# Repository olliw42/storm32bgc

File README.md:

STorM32 BGC
===========

<strong>STM32 32-bit microcontroller based 3-axis brushless gimbal controller board</strong>

scheme and design by OlliW (except of STorM32 v4.1)<br>
v0.17: layout by Martinez and OlliW<br>
v4.1: design by KrattWorks

latest board version: v3.3, v4.1

the STorM32 BGC boards and all other hardware published here are open source hardware, under the terms of the TAPR Open Hardware License as published by the Free Hardware Foundation, see http://www.tapr.org/ohl.html

the firmwares are free and the GUI is open source, for the details of the terms of usage/licenses see <a href="http://www.olliw.eu/2013/storm32bgc">here</a>

<strong>further resources:</strong><br>- project web page http://www.olliw.eu/2013/storm32bgc/<br>- thread at rcgroups http://www.rcgroups.com/forums/showthread.php?t=2055844<br>- wiki for the documentation http://www.olliw.eu/storm32bgc-wiki/

## v4.1 Board

Board specifically made for NT and TSTorM32 setups, with on-board motor drivers.

## v3.3 Boards

Boards specifically made for NT and TSTorM32 setups.

### STorM32 v3.3m/i

General purpose version.

### STorM32 Raspberry Pi Hat

Hat for the Raspberry Pi.

### STorM32 Micro Series

Series of stackable boards with 20x20 mm hole pattern: Main board, NT Motor-Encoder module, NT Triple Motor module, NT Logger module. 

<strong>changes in v3.3:</strong><br>- board specifically designed for NT and T-STorM32<br>- no motor drivers on board<br>- 3 NT plugs to make it easy to connect several NT modules<br>- NT-X plug carrying also the battery voltage<br>- 5 V power rail on the NT bus, with sufficient "juice"<br>- Rx&Tx on NT bus swapped, to avoid cable crossing to connect with NT modules<br>- support of stacking with a "high-power" extension board<br>- MPU9250 on board, spi (no i2c anymore!)<br>- firmware update procedure via USB<br>- ESP8266 port for WIFI connectability<br>- CAN bus port<br>- no BOOT0 button, smaller RESET button<br>- 0402 size parts<br>- board size as small as I could get it with a 2 layer design: 40 x 25 mm<br>- mounting holes, 3 mm diameter, 35 mm apart

## v1.x Boards

<strong>changes in v1.3:</strong><br>- voltage regulator in DPak package<br>- AUX2 instead of 3.3V pin at AUX port<br>- solder jumper to disconnect bluetooth led<br>- values of resistors R12,R13,R22 changed
<br><strong>changes in v1.2:</strong><br>- minor issues of v1.1 corrected<br>- Futaba S-bus support<br>- Spektrum sattelite connector<br>- usb disconnect network modified to suite F4 processors (thanks ala42!)<br>- usb voltage protection diode added (as in v0.17)<br>- further minor changes in scheme and layout
<br><strong>changes in v1.1:</strong><br>- reverse voltage protection added<br>- layout supports TC4452 motor drivers in DFN package for increased power capabilities<br>- high-side pnp open collector output for driving an IR led added<br>- additional connector for I2C#2 port added<br>- larger solder holes and pads for battery power connection<br>- improved pin arrangement for easier use

## Pictures

<strong>pictures of the v2.4 board</strong><br>

<strong>pictures of the v1.2 board (with DFN packages) and v1.3 board (with SOIC packages):</strong><br>

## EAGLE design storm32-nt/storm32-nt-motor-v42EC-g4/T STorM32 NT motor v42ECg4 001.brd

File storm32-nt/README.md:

STorM32 Boards NT Series and NT Modules
==============

Schemes and designs by OlliW (with exceptin of the STorM32 v4.1 board). The STorM32 v4.1 board is design by [KrattWorks](https://www.krattworks.com/), [2](https://bitbucket.org/teamkrattworks/hw_storm32_v4/src/master/release/storm32-nt-v4_1/).<br>

The STorM32 boards offered in this folder are published as open source hardware, under the terms of the TAPR Open Hardware License as published by the Free Hardware Foundation, see http://www.tapr.org/ohl.html.

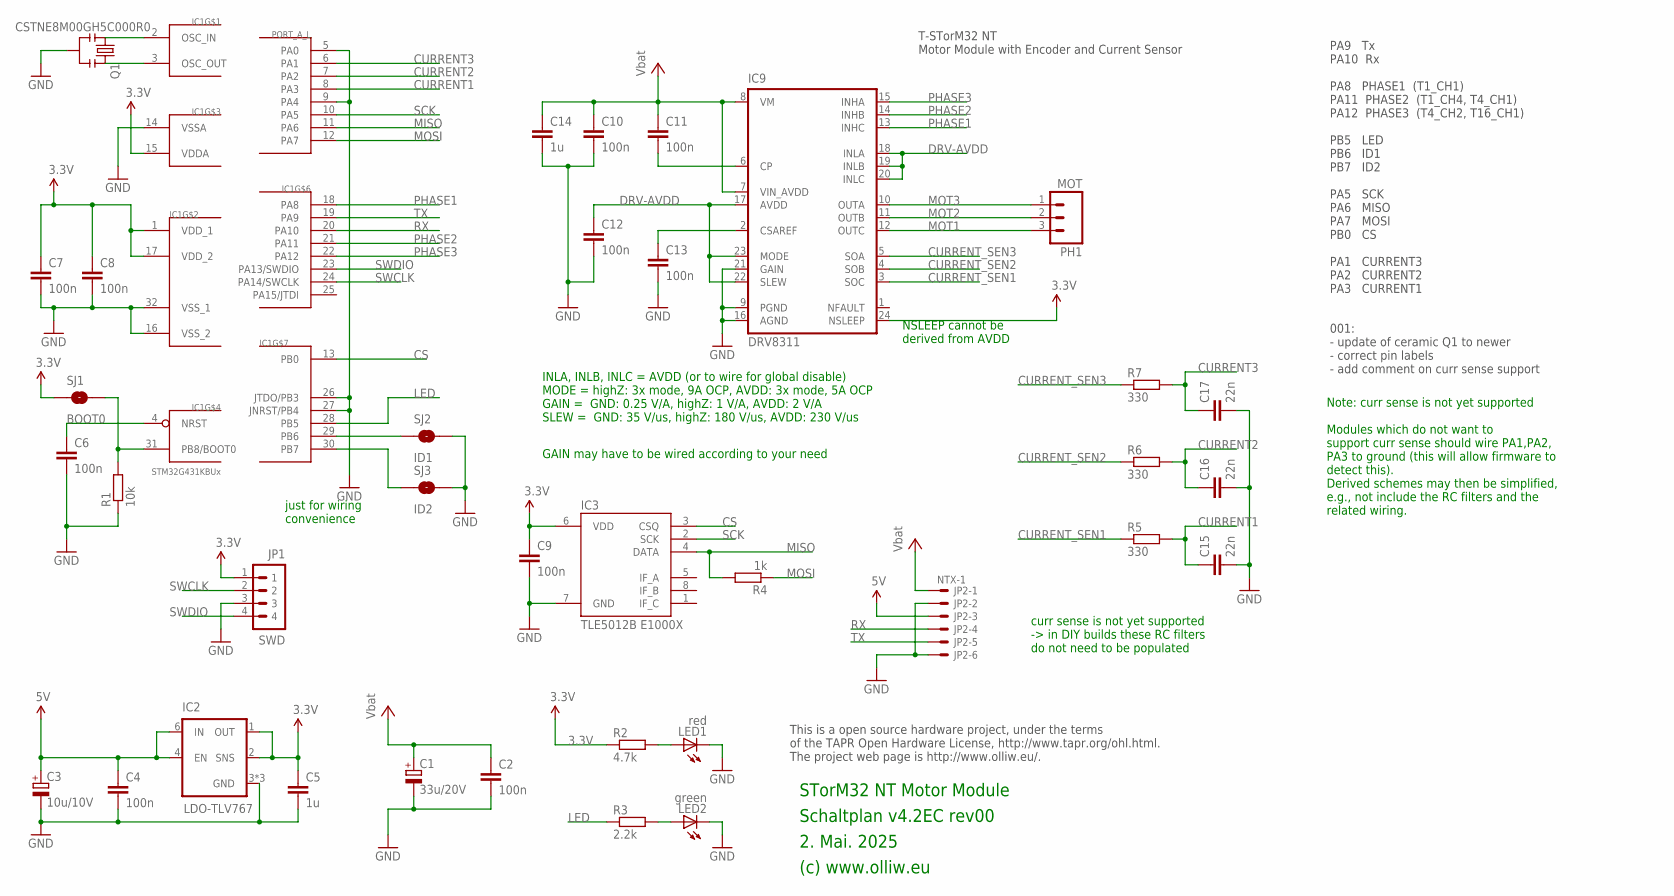
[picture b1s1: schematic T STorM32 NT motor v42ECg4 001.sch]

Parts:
C1: 33u/20V; SMC_C
C2, C4: 100n; C0603
C3: 10u/10V; SMC_B
C5, C14: 1u; C0603
C6, C7, C8, C9, C10, C11, C12, C13: 100n; C0402
C15, C16, C17: 22n; C0402
IC1: STM32G431KBUx; UFQFPN32
IC2: LDO-TLV767; WSON-6-2X2
IC3: TLE5012B E1000X; SO08
IC9: DRV8311; QFN(WQFN)24-3X3-DRV8311
JP1: SWD; 4X1_1P27_OCT_BILEX
JP2: NTX-1; SM06B-SRSS-TB
LED1: red; CHIPLED_0603
LED2: green; CHIPLED_0603
PH1: MOT; 1X03_NO_SILK
Q1: CSTNE8M00GH5C000R0; RESONATOR-SMD
R1: 10k; R0402
R2: 4.7k; R0402
R3: 2.2k; R0402
R4: 1k; R0402
R5, R6, R7: 330; R0402
SJ1: BOOT0; SJ_2S-NO
SJ2: ID1; SJ_2S-NO
SJ3: ID2; SJ_2S-NO

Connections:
3.3V: C5.1, C7.1, C8.1, C9.1, IC1.1 (VDD_1), IC1.15 (VDDA), IC1.17 (VDD_2), IC2.1 (OUT), IC2.2 (SNS), IC3.6 (VDD), IC9.24 (NSLEEP), JP1.1, R2.1, SJ1.1
5V: C3.+, C4.1, IC2.4 (EN), IC2.6 (IN), JP2.3
CS: IC1.13 (PB0), IC3.3 (CSQ)
CURRENT1: C15.1, IC1.8 (PA3), R5.2
CURRENT2: C16.1, IC1.7 (PA2), R6.2
CURRENT3: C17.1, IC1.6 (PA1), R7.2
CURRENT_SEN1: IC9.3 (SOC), R5.1
CURRENT_SEN2: IC9.4 (SOB), R6.1
CURRENT_SEN3: IC9.5 (SOA), R7.1
DRV-AVDD: C12.1, IC9.17 (AVDD), IC9.18 (INLA), IC9.19 (INLB), IC9.20 (INLC), IC9.22 (SLEW), IC9.23 (MODE)
DRV-CP: C11.2, IC9.6 (CP)
DRV-CSAREF: C13.1, IC9.2 (CSAREF)
GND: C1.-, C2.2, C3.-, C4.2, C5.2, C6.2, C7.2, C8.2, C9.2, C10.2, C12.2, C13.2, C14.2, C15.2, C16.2, C17.2, IC1.5 (PA0), IC1.9 (PA4), IC1.14 (VSSA), IC1.16 (VSS_2), IC1.26 (JTDO/PB3), IC1.27 (JNRST/PB4), IC1.32 (VSS_1), IC2.3 (GND), IC2.5 (GND), IC2.7 (GND), IC3.7 (GND), IC9.9 (PGND), IC9.16 (AGND), IC9.21 (GAIN), JP1.3, JP2.2, JP2.6, LED1.C, LED2.C, Q1.2, R1.1, SJ2.2, SJ3.2
ID1: IC1.29 (PB6), SJ2.1
ID2: IC1.30 (PB7), SJ3.1
LED: IC1.28 (PB5), R3.1
MISO: IC1.11 (PA6), IC3.4 (DATA), R4.2
MOSI: IC1.12 (PA7), R4.1
MOT1: IC9.12 (OUTC), PH1.3
MOT2: IC9.11 (OUTB), PH1.2
MOT3: IC9.10 (OUTA), PH1.1
unnamed: C6.1, IC1.4 (NRST)
unnamed: IC1.31 (PB8/BOOT0), R1.2, SJ1.2
unnamed: IC1.2 (OSC_IN), Q1.1
unnamed: IC1.3 (OSC_OUT), Q1.3
unnamed: LED1.A, R2.2
unnamed: LED2.A, R3.2
PHASE1: IC1.18 (PA8), IC9.13 (INHC)
PHASE2: IC1.21 (PA11), IC9.14 (INHB)
PHASE3: IC1.22 (PA12), IC9.15 (INHA)
RX: IC1.20 (PA10), JP2.4
SCK: IC1.10 (PA5), IC3.2 (SCK)
SWCLK: IC1.24 (PA14/SWCLK), JP1.2
SWDIO: IC1.23 (PA13/SWDIO), JP1.4
TX: IC1.19 (PA9), JP2.5
VBAT: C1.+, C2.1, C10.1, C11.1, C14.1, IC9.7 (VIN_AVDD), IC9.8 (VM), JP2.1

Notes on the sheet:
2. Mai. 2025
(c) www.olliw.eu
STorM32 NT Motor Module
Schaltplan v4.2EC rev00
This is a open source hardware project, under the terms of the TAPR Open Hardware License, http://www.tapr.org/ohl.html. The project web page is http://www.olliw.eu/.
T-STorM32 NT Motor Module with Encoder and Current Sensor
PA9 Tx PA10 Rx PA8 PHASE1 (T1_CH1) PA11 PHASE2 (T1_CH4, T4_CH1) PA12 PHASE3 (T4_CH2, T16_CH1) PB5 LED PB6 ID1 PB7 ID2 PA5 SCK PA6 MISO PA7 MOSI PB0 CS PA1 CURRENT3 PA2 CURRENT2 PA3 CURRENT1
INLA, INLB, INLC = AVDD (or to wire for global disable) MODE = highZ: 3x mode, 9A OCP, AVDD: 3x mode, 5A OCP GAIN = GND: 0.25 V/A, highZ: 1 V/A, AVDD: 2 V/A SLEW = GND: 35 V/us, highZ: 180 V/us, AVDD: 230 V/us
NSLEEP cannot be derived from AVDD
just for wiring convenience
curr sense is not yet supported -> in DIY builds these RC filters do not need to be populated
001: - update of ceramic Q1 to newer - correct pin labels - add comment on curr sense support
GAIN may have to be wired according to your need
Note: curr sense is not yet supported Modules which do not want to support curr sense should wire PA1,PA2, PA3 to ground (this will allow firmware to detect this). Derived schemes may then be simplified, e.g., not include the RC filters and the related wiring.

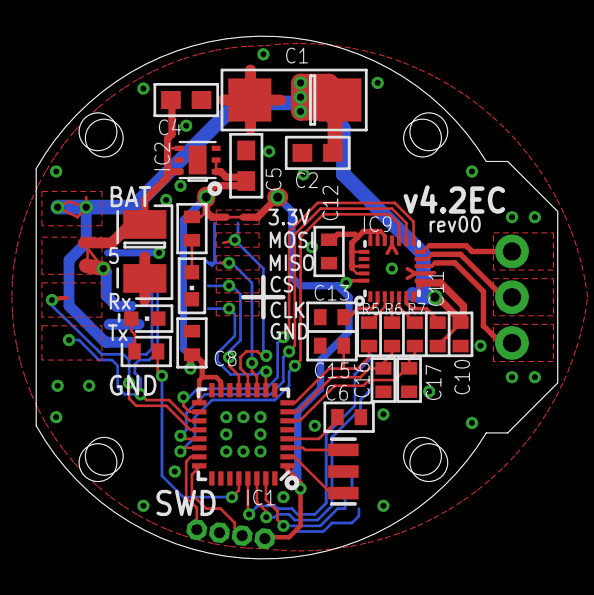
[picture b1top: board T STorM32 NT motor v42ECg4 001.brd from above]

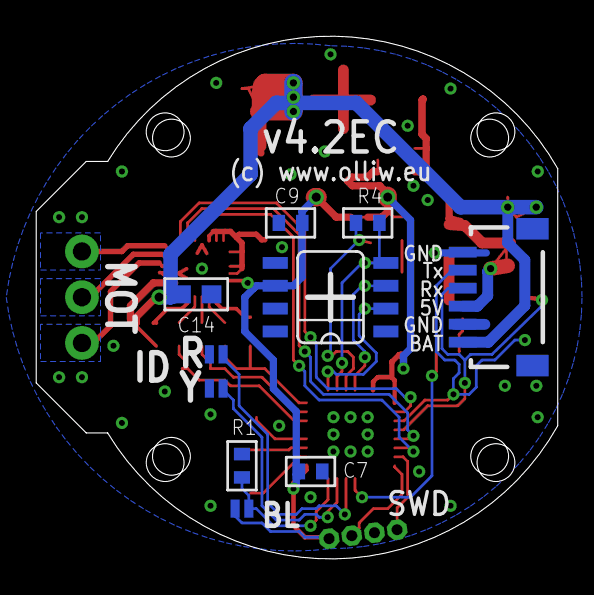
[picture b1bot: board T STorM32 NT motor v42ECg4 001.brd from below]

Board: 2 copper layers, 29.0 x 29.0 mm, 37 parts (10 on the bottom side), 36 nets.

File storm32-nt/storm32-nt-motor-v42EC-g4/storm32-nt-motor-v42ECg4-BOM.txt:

Stückliste exportiert aus C:/Users/Olli/Documents/GitHub/storm32bgc/storm32-nt/storm32-nt-motor-v42EC-g4/T STorM32 NT motor v42ECg4 001.sch am 07.05.2025 07:32

Part Value              Device              Package                 Description                                                 
C1   33u/20V            CPOL-EUSMCC         SMC_C                   POLARIZED CAPACITOR, European symbol                        
C2   100n               C-EUC0603           C0603                   CAPACITOR, European symbol                                  
C3   10u/10V            CPOL-EUSMCB         SMC_B                   POLARIZED CAPACITOR, European symbol                        
C4   100n               C-EUC0603           C0603                   CAPACITOR, European symbol                                  
C5   1u                 C-EUC0603           C0603                   CAPACITOR, European symbol                                  
C6   100n               C-EUC0402           C0402                   CAPACITOR, European symbol                                  
C7   100n               C-EUC0402           C0402                   CAPACITOR, European symbol                                  
C8   100n               C-EUC0402           C0402                   CAPACITOR, European symbol                                  
C9   100n               C-EUC0402           C0402                   CAPACITOR, European symbol                                  
C10  100n               C-EUC0402           C0402                   CAPACITOR, European symbol                                  
C11  100n               C-EUC0402           C0402                   CAPACITOR, European symbol                                  
C12  100n               C-EUC0402           C0402                   CAPACITOR, European symbol                                  
C13  100n               C-EUC0402           C0402                   CAPACITOR, European symbol                                  
C14  1u                 C-EUC0603           C0603                   CAPACITOR, European symbol                                  
C15  22n                C-EUC0402           C0402                   CAPACITOR, European symbol                                  
C16  22n                C-EUC0402           C0402                   CAPACITOR, European symbol                                  
C17  22n                C-EUC0402           C0402                   CAPACITOR, European symbol                                  
IC1  STM32G431KBUx      STM32G4X1KX         UFQFPN32                                                                            
IC2  LDO-TLV767         LDO-TLV767          WSON-6-2X2                                                                          
IC3  TLE5012B E1000X    TLE5012B            SO08                                                                                
IC9  DRV8311            DRV8311             QFN(WQFN)24-3X3-DRV8311                                                             
JP1  SWD                P4X1_1P27-OCT_BILEX 4X1_1P27_OCT_BILEX                                                                  
JP2  NTX-1              SM06B-SRSS-TB       SM06B-SRSS-TB           Disconnectable Crimp style connector, 1.0mm pitch6 contacts 
LED1 red                LEDCHIPLED_0603     CHIPLED_0603            LED                                                         
LED2 green              LEDCHIPLED_0603     CHIPLED_0603            LED                                                         
PH1  MOT                M031X03_NO_SILK     1X03_NO_SILK            Header 3                                                    
Q1   CSTNE8M00GH5C000R0 RESONATORSMD        RESONATOR-SMD           Resonator                                                   
R1   10k                R-EU_R0402          R0402                   RESISTOR, European symbol                                   
R2   4.7k               R-EU_R0402          R0402                   RESISTOR, European symbol                                   
R3   2.2k               R-EU_R0402          R0402                   RESISTOR, European symbol                                   
R4   1k                 R-EU_R0402          R0402                   RESISTOR, European symbol                                   
R5   330                R-EU_R0402          R0402                   RESISTOR, European symbol                                   
R6   330                R-EU_R0402          R0402                   RESISTOR, European symbol                                   
R7   330                R-EU_R0402          R0402                   RESISTOR, European symbol                                   
SJ1  BOOT0              SOLDERJUMPERNO      SJ_2S-NO                Solder Jumper                                               
SJ2  ID1                SOLDERJUMPERNO      SJ_2S-NO                Solder Jumper                                               
SJ3  ID2                SOLDERJUMPERNO      SJ_2S-NO                Solder Jumper

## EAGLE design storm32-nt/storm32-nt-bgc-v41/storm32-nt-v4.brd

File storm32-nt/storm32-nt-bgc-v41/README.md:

STorM32 Board v4.1
==================

The STorM32 v4.1 board is design by [KrattWorks](https://www.krattworks.com/).

TeamKrattWorks' repository: https://bitbucket.org/teamkrattworks/hw_storm32_v4/src/master/release/storm32-nt-v4_1/.

This STorM32 board is published as open source hardware, under the terms of the TAPR Open Hardware License as published by the Free Hardware Foundation, see http://www.tapr.org/ohl.html.

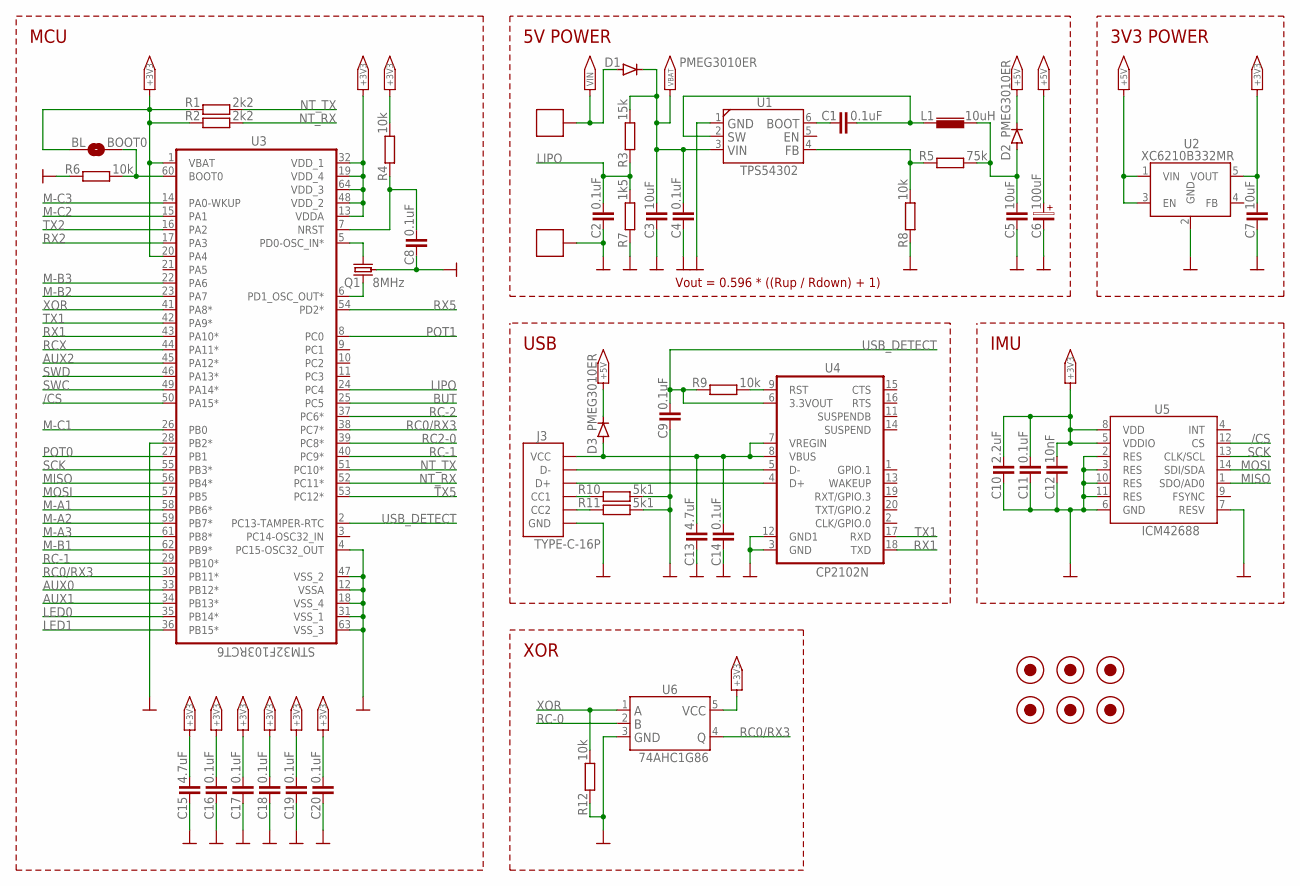
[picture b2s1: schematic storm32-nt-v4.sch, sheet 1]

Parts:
BL: BOOT0; __SPARKFUN2_SJ_2S-NO
C1, C2, C8, C9, C11, C14, C16, C17, C18, C19, C20: 0.1uF; 0402[1005-METRIC]
C3: 10uF; 1206[3216-METRIC]; VOLTAGE 63; MOUSER 81-GRM32ER71J106MA2L
C4: 0.1uF; 0603[1608-METRIC]
C5, C7: 10uF; 0603[1608-METRIC]
C6: 100uF; 1206[3216-METRIC]-POL
C10: 2.2uF; 0402[1005-METRIC]
C12: 10nF; 0402[1005-METRIC]
C13, C15: 4.7uF; 0402[1005-METRIC]
D1, D2, D3: PMEG3010ER; SOD-123
FIDUCIAL1, FIDUCIAL2, FIDUCIAL3, FIDUCIAL4, FIDUCIAL5, FIDUCIAL6: FIDUCIAL
J1: +; 1
J2: -; 1
J3: TYPE-C-16P
L1: 10uH; 4X4
Q1: 8MHz; RESONATOR
R1, R2: 2k2; 0402[1005-METRIC]
R3: 15k; 0402[1005-METRIC]
R4, R6, R8, R9, R12: 10k; 0402[1005-METRIC]
R5: 75k; 0402[1005-METRIC]
R7: 1k5; 0402[1005-METRIC]
R10, R11: 5k1; 0402[1005-METRIC]
U1: TPS54302; SOT-23-6
U2: XC6210B332MR; SOT-23-5
U3: STM32F103RCT6; QFP50P1200X1200X160-64N
U4: CP2102N; QFN-20
U5: ICM42688; LGA14
U6: 74AHC1G86; SOT-23-5

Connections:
+3V3: BL.2, C7.P$1 (1), C10.P$1 (1), C11.P$1 (1), C12.P$1 (1), C15.P$1 (1), C16.P$1 (1), C17.P$1 (1), C18.P$1 (1), C19.P$1 (1), C20.P$1 (1), R1.P$1, R2.P$1, R4.P$2, U2.5 (VOUT), U3.1 (VBAT), U3.13 (VDDA), U3.19 (VDD_4), U3.20 (PA4), U3.32 (VDD_1), U3.48 (VDD_2), U3.64 (VDD_3), U5.5 (VDDIO), U5.8 (VDD), U6.5; also elsewhere on the board
+5V: C6.P, D2.C, D3.C, U2.1 (VIN), U2.3 (EN); also elsewhere on the board
/CS: U3.50 (PA15*), U5.12 (CS)
AUX0: U3.33 (PB12*); also elsewhere on the board
AUX1: U3.34 (PB13*); also elsewhere on the board
AUX2: U3.45 (PA12*)
BUT: U3.25 (PC5); also elsewhere on the board
GND: C2.P$2 (2), C3.P$2 (2), C4.P$2 (2), C5.P$2 (2), C6.N, C7.P$2 (2), C8.P$2 (2), C9.P$2 (2), C10.P$2 (2), C11.P$2 (2), C12.P$2 (2), C13.P$2 (2), C14.P$2 (2), C15.P$2 (2), C16.P$2 (2), C17.P$2 (2), C18.P$2 (2), C19.P$2 (2), C20.P$2 (2), J2.1, J2.1A, J3.A1 (GND), J3.A12 (GND), J3.B1 (GND), J3.B12 (GND), J3.G1 (GND), J3.G2 (GND), J3.G3 (GND), J3.G4 (GND), Q1.G (GND), R6.P$1, R7.P$1, R8.P$1, R10.P$2, R11.P$2, R12.P$2, U1.1, U2.2 (GND), U3.4 (PC15-OSC32_OUT), U3.12 (VSSA), U3.18 (VSS_4), U3.28 (PB2*), U3.31 (VSS_1), U3.47 (VSS_2), U3.63 (VSS_3), U4.3 (GND), U4.12 (GND1), U5.2 (RES), U5.3 (RES), U5.6 (GND), U5.7 (RESV), U5.10 (RES), U5.11 (RES), U6.3; also elsewhere on the board
LED0: U3.35 (PB14*); also elsewhere on the board
LED1: U3.36 (PB15*); also elsewhere on the board
LIPO: C2.P$1 (1), R3.P$1, R7.P$2, U3.24 (PC4)
M-A1: U3.58 (PB6*); also elsewhere on the board
M-A2: U3.59 (PB7*); also elsewhere on the board
M-A3: U3.61 (PB8*); also elsewhere on the board
M-B1: U3.62 (PB9*); also elsewhere on the board
M-B2: U3.23 (PA7); also elsewhere on the board
M-B3: U3.22 (PA6); also elsewhere on the board
M-C1: U3.26 (PB0); also elsewhere on the board
M-C2: U3.15 (PA1); also elsewhere on the board
M-C3: U3.14 (PA0-WKUP); also elsewhere on the board
MISO: U3.56 (PB4*), U5.1 (SDO/AD0)
MOSI: U3.57 (PB5), U5.14 (SDI/SDA)
unnamed: J3.A5 (CC1), R10.P$1
unnamed: J3.B5 (CC2), R11.P$1
unnamed: C1.P$1 (1), L1.1, U1.2
unnamed: Q1.1, U3.6 (PD1_OSC_OUT*)
unnamed: Q1.2, U3.5 (PD0-OSC_IN*)
unnamed: C8.P$1 (1), R4.P$1, U3.7 (NRST)
unnamed: C1.P$2 (2), U1.6
unnamed: J3.A6 (D+), J3.B6 (D+), U4.4 (D+)
unnamed: J3.A7 (D-), J3.B7 (D-), U4.5 (D-)
unnamed: C13.P$1 (1), C14.P$1 (1), D3.A, J3.A4 (VCC), J3.A9 (VCC), J3.B4 (VCC), J3.B9 (VCC), U4.7 (VREGIN), U4.8 (VBUS)
unnamed: R9.P$2, U4.9 (RST)
unnamed: R5.P$1, R8.P$2, U1.4
unnamed: C5.P$1 (1), D2.A, L1.2, R5.P$2
unnamed: BL.1, R6.P$2, U3.60 (BOOT0)
NT_RX: R2.P$2, U3.52 (PC11*); also elsewhere on the board
NT_TX: R1.P$2, U3.51 (PC10*); also elsewhere on the board
POT0: U3.27 (PB1); also elsewhere on the board
POT1: U3.8 (PC0); also elsewhere on the board
RC0/RX3: U3.30 (PB11*), U3.38 (PC7*), U6.4
RC2-0: U3.39 (PC8*); also elsewhere on the board
RC-0: U6.2; also elsewhere on the board
RC-1: U3.29 (PB10*), U3.40 (PC9*); also elsewhere on the board
RC-2: U3.37 (PC6*); also elsewhere on the board
RCX: U3.44 (PA11*)
RX1: U3.43 (PA10*), U4.18 (TXD)
RX2: U3.17 (PA3); also elsewhere on the board
RX5: U3.54 (PD2*); also elsewhere on the board
SCK: U3.55 (PB3*), U5.13 (CLK/SCL)
SWC: U3.49 (PA14*); also elsewhere on the board
SWD: U3.46 (PA13*); also elsewhere on the board
TX1: U3.42 (PA9*), U4.17 (RXD)
TX2: U3.16 (PA2); also elsewhere on the board
TX5: U3.53 (PC12*); also elsewhere on the board
USB_DETECT: C9.P$1 (1), R9.P$1, U3.2 (PC13-TAMPER-RTC), U4.6 (3.3VOUT)
VBAT: C3.P$1 (1), C4.P$1 (1), D1.C, R3.P$2, U1.3; also elsewhere on the board
VIN: D1.A, J1.1, J1.1A; also elsewhere on the board
XOR: R12.P$1, U3.41 (PA8*), U6.1

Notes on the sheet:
Vout = 0.596 * ((Rup / Rdown) + 1)
5V POWER
USB
3V3 POWER
MCU
IMU
XOR

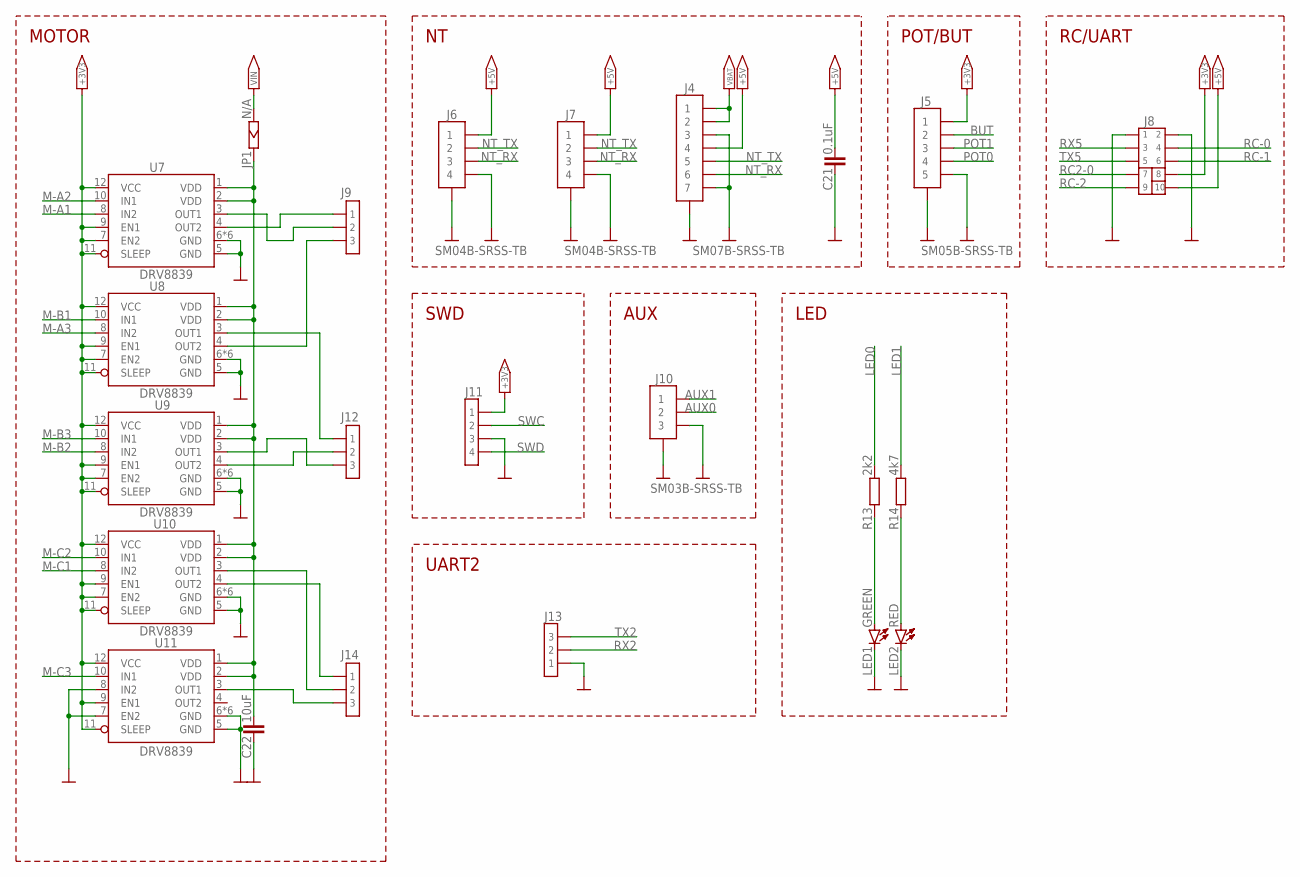
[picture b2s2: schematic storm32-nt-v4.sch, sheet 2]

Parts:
C21: 0.1uF; 0402[1005-METRIC]
C22: 10uF; 1206[3216-METRIC]; VOLTAGE 63; MOUSER 81-GRM32ER71J106MA2L
J4: SM07B-SRSS-TB
J5: SM05B-SRSS-TB
J6, J7: SM04B-SRSS-TB
J8: HEADER; 2X5
J9, J12, J13, J14: HEADER_THT_2.54X1N_MALE-03-2.54-2.54; HEADER_THT_2.54X1N_MALE-03
J10: SM03B-SRSS-TB
J11: HEADER_THT_1.27X1N_MALE-04-1.27-1.27; HEADER_THT_1.27X1N_MALE-04
JP1: N/A; 0603[1608-METRIC]-0OHM-OFF
LED1: GREEN; 0603[1608-METRIC]-DIODE
LED2: RED; 0603[1608-METRIC]-DIODE
R13: 2k2; 0402[1005-METRIC]
R14: 4k7; 0402[1005-METRIC]
U7, U8, U9, U10, U11: DRV8839; WSON12

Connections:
+3V3: J5.1, J8.8, J11.1, U7.7 (EN2), U7.9 (EN1), U7.11 (SLEEP), U7.12 (VCC), U8.7 (EN2), U8.9 (EN1), U8.11 (SLEEP), U8.12 (VCC), U9.7 (EN2), U9.9 (EN1), U9.11 (SLEEP), U9.12 (VCC), U10.7 (EN2), U10.9 (EN1), U10.11 (SLEEP), U10.12 (VCC), U11.9 (EN1), U11.11 (SLEEP), U11.12 (VCC); also elsewhere on the board
+5V: C21.P$1 (1), J4.4, J6.1, J7.1, J8.10; also elsewhere on the board
AUX0: J10.2; also elsewhere on the board
AUX1: J10.1; also elsewhere on the board
BUT: J5.2; also elsewhere on the board
GND: C21.P$2 (2), C22.P$2 (2), J4.3, J4.7, J4.FIT@1, J4.FIT@2, J5.5, J5.FIT@1, J5.FIT@2, J6.4, J6.FIT@1, J6.FIT@2, J7.4, J7.FIT@1, J7.FIT@2, J8.1, J8.2, J10.3, J10.FIT@1, J10.FIT@2, J11.3, J13.1, LED1.C, LED2.C, U7.5 (GND), U7.6 (GND), U7.GND1 (GND), U7.GND2 (GND), U7.GND3 (GND), U7.GND4 (GND), U7.GND5 (GND), U8.5 (GND), U8.6 (GND), U8.GND1 (GND), U8.GND2 (GND), U8.GND3 (GND), U8.GND4 (GND), U8.GND5 (GND), U9.5 (GND), U9.6 (GND), U9.GND1 (GND), U9.GND2 (GND), U9.GND3 (GND), U9.GND4 (GND), U9.GND5 (GND), U10.5 (GND), U10.6 (GND), U10.GND1 (GND), U10.GND2 (GND), U10.GND3 (GND), U10.GND4 (GND), U10.GND5 (GND), U11.5 (GND), U11.6 (GND), U11.7 (EN2), U11.8 (IN2), U11.GND1 (GND), U11.GND2 (GND), U11.GND3 (GND), U11.GND4 (GND), U11.GND5 (GND); also elsewhere on the board
LED0: R13.P$2; also elsewhere on the board
LED1: R14.P$2; also elsewhere on the board
M-A1: U7.8 (IN2); also elsewhere on the board
M-A2: U7.10 (IN1); also elsewhere on the board
M-A3: U8.8 (IN2); also elsewhere on the board
M-B1: U8.10 (IN1); also elsewhere on the board
M-B2: U9.8 (IN2); also elsewhere on the board
M-B3: U9.10 (IN1); also elsewhere on the board
M-C1: U10.8 (IN2); also elsewhere on the board
M-C2: U10.10 (IN1); also elsewhere on the board
M-C3: U11.10 (IN1); also elsewhere on the board
unnamed: LED1.A, R13.P$1
unnamed: C22.P$1 (1), JP1.P$2, U7.1 (VDD), U7.2 (VDD), U8.1 (VDD), U8.2 (VDD), U9.1 (VDD), U9.2 (VDD), U10.1 (VDD), U10.2 (VDD), U11.1 (VDD), U11.2 (VDD)
unnamed: LED2.A, R14.P$1
unnamed: J9.1, U7.4 (OUT2)
unnamed: J9.2, U7.3 (OUT1)
unnamed: J9.3, U8.4 (OUT2)
unnamed: J12.1, U8.3 (OUT1)
unnamed: J12.2, U9.4 (OUT2)
unnamed: J12.3, U9.3 (OUT1)
unnamed: J14.2, U10.3 (OUT1)
unnamed: J14.1, U10.4 (OUT2)
unnamed: J14.3, U11.3 (OUT1)
NT_RX: J4.6, J6.3, J7.3; also elsewhere on the board
NT_TX: J4.5, J6.2, J7.2; also elsewhere on the board
POT0: J5.4; also elsewhere on the board
POT1: J5.3; also elsewhere on the board
RC2-0: J8.7; also elsewhere on the board
RC-0: J8.4; also elsewhere on the board
RC-1: J8.6; also elsewhere on the board
RC-2: J8.9; also elsewhere on the board
RX2: J13.2; also elsewhere on the board
RX5: J8.3; also elsewhere on the board
SWC: J11.2; also elsewhere on the board
SWD: J11.4; also elsewhere on the board
TX2: J13.3; also elsewhere on the board
TX5: J8.5; also elsewhere on the board
VBAT: J4.1, J4.2; also elsewhere on the board
VIN: JP1.P$1; also elsewhere on the board

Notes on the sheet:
MOTOR
POT/BUT
SWD
AUX
UART2
LED
RC/UART

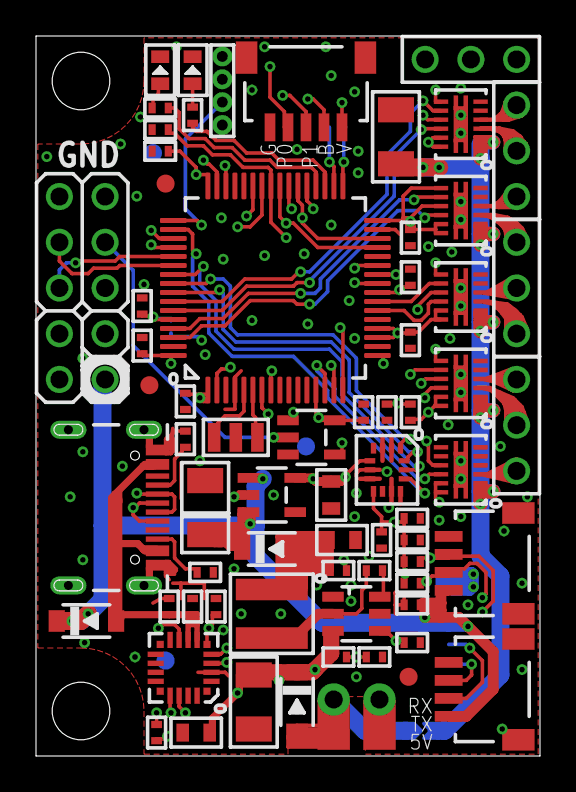
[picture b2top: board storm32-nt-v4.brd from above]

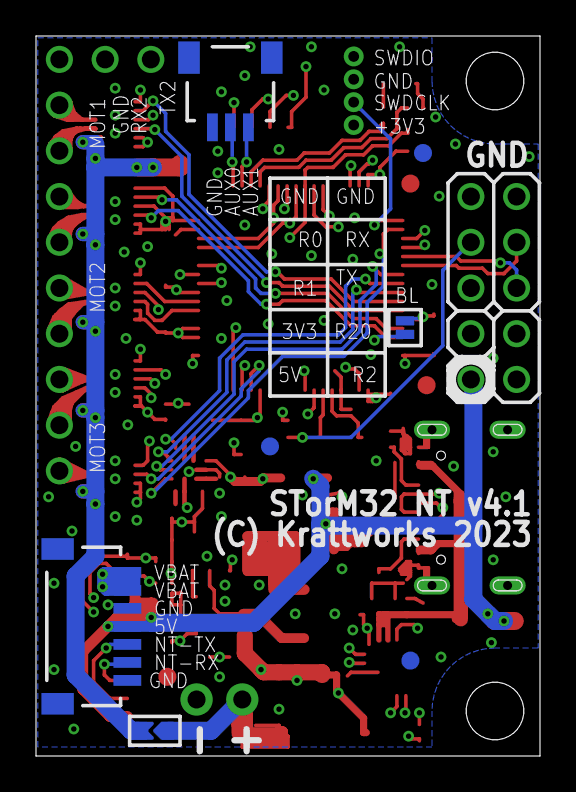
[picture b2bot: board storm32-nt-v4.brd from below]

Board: 4 copper layers, 28.0 x 40.0 mm, 77 parts (7 on the bottom side), 69 nets.

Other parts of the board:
FRAMEBRD1: A5L-LOC

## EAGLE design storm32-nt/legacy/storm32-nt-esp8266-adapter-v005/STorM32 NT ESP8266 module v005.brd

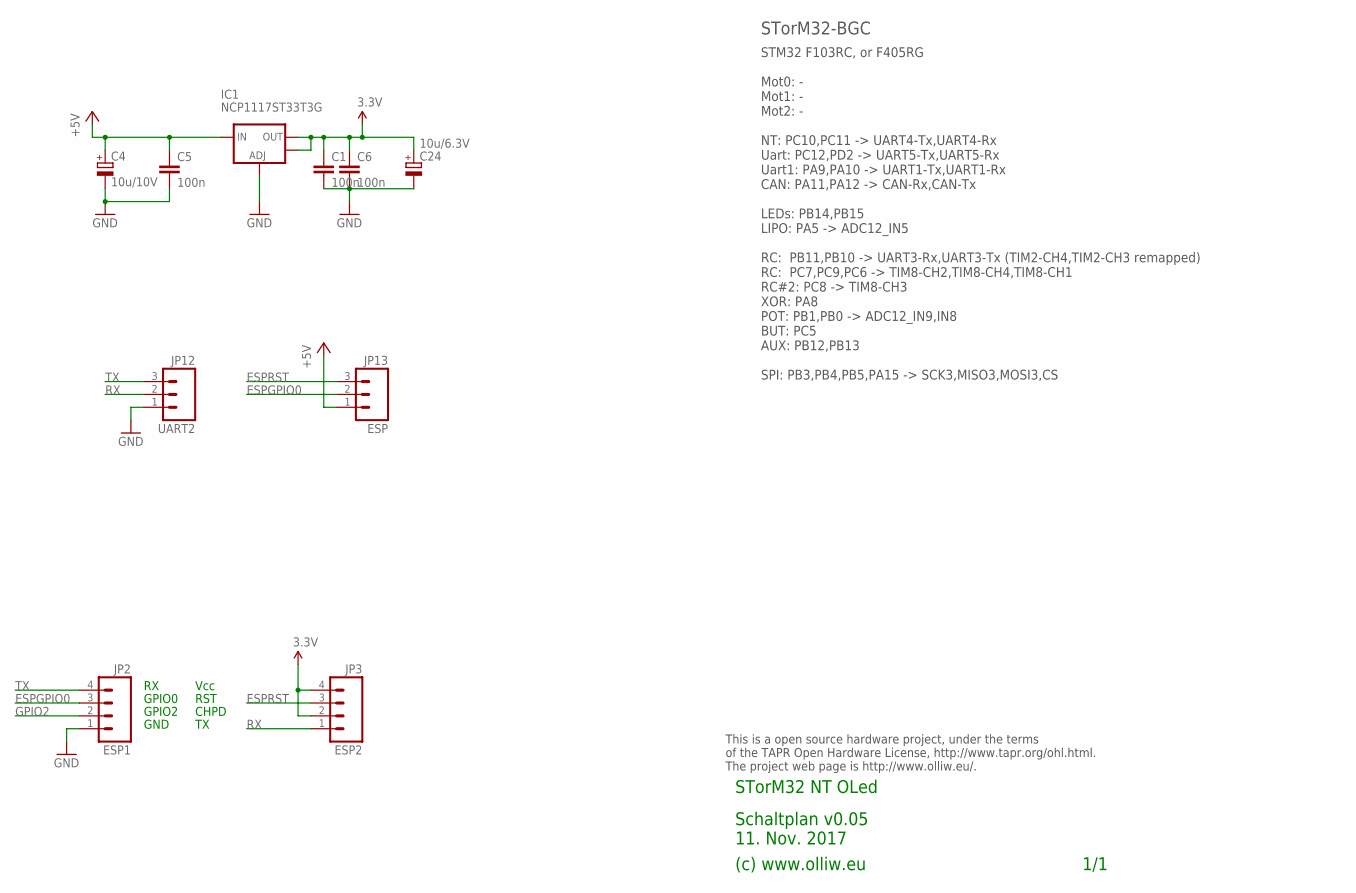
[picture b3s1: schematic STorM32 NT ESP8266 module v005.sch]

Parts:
C1, C5, C6: 100n; C0603
C4: 10u/10V; SMC_A
C24: 10u/6.3V; SMC_B
IC1: NCP1117ST33T3G; SOT223
JP2: ESP1; 1X04_NO_SILK
JP3: ESP2; 1X04_NO_SILK
JP12: UART2; 1X03_NO_SILK
JP13: ESP; 1X03_NO_SILK

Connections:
3.3V: C1.1, C6.1, C24.+, IC1.2 (OUT), IC1.4 (OUT), JP3.2, JP3.4
+5V: C4.+, C5.1, IC1.3 (IN), JP13.1
ESPGPIO0: JP2.3, JP13.2
ESPRST: JP3.3, JP13.3
GND: C1.2, C4.-, C5.2, C6.2, C24.-, IC1.1 (ADJ), JP2.1, JP12.1
GPIO2: JP2.2
RX: JP3.1, JP12.2
TX: JP2.4, JP12.3

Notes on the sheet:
(c) www.olliw.eu
STorM32 NT OLed
This is a open source hardware project, under the terms of the TAPR Open Hardware License, http://www.tapr.org/ohl.html. The project web page is http://www.olliw.eu/.
STM32 F103RC, or F405RG Mot0: - Mot1: - Mot2: - NT: PC10,PC11 -> UART4-Tx,UART4-Rx Uart: PC12,PD2 -> UART5-Tx,UART5-Rx Uart1: PA9,PA10 -> UART1-Tx,UART1-Rx CAN: PA11,PA12 -> CAN-Rx,CAN-Tx LEDs: PB14,PB15 LIPO: PA5 -> ADC12_IN5 RC: PB11,PB10 -> UART3-Rx,UART3-Tx (TIM2-CH4,TIM2-CH3 remapped) RC: PC7,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
STorM32-BGC
1/1
Schaltplan v0.05 11. Nov. 2017
GPIO0
GPIO2
GND
Vcc
RST
CHPD

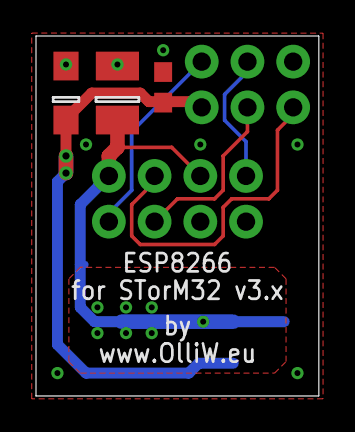
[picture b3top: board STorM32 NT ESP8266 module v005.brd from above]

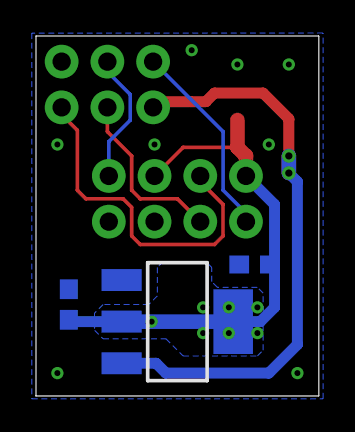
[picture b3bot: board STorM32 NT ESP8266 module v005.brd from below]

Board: 2 copper layers, 15.7 x 20.0 mm, 10 parts (3 on the bottom side), 7 nets.

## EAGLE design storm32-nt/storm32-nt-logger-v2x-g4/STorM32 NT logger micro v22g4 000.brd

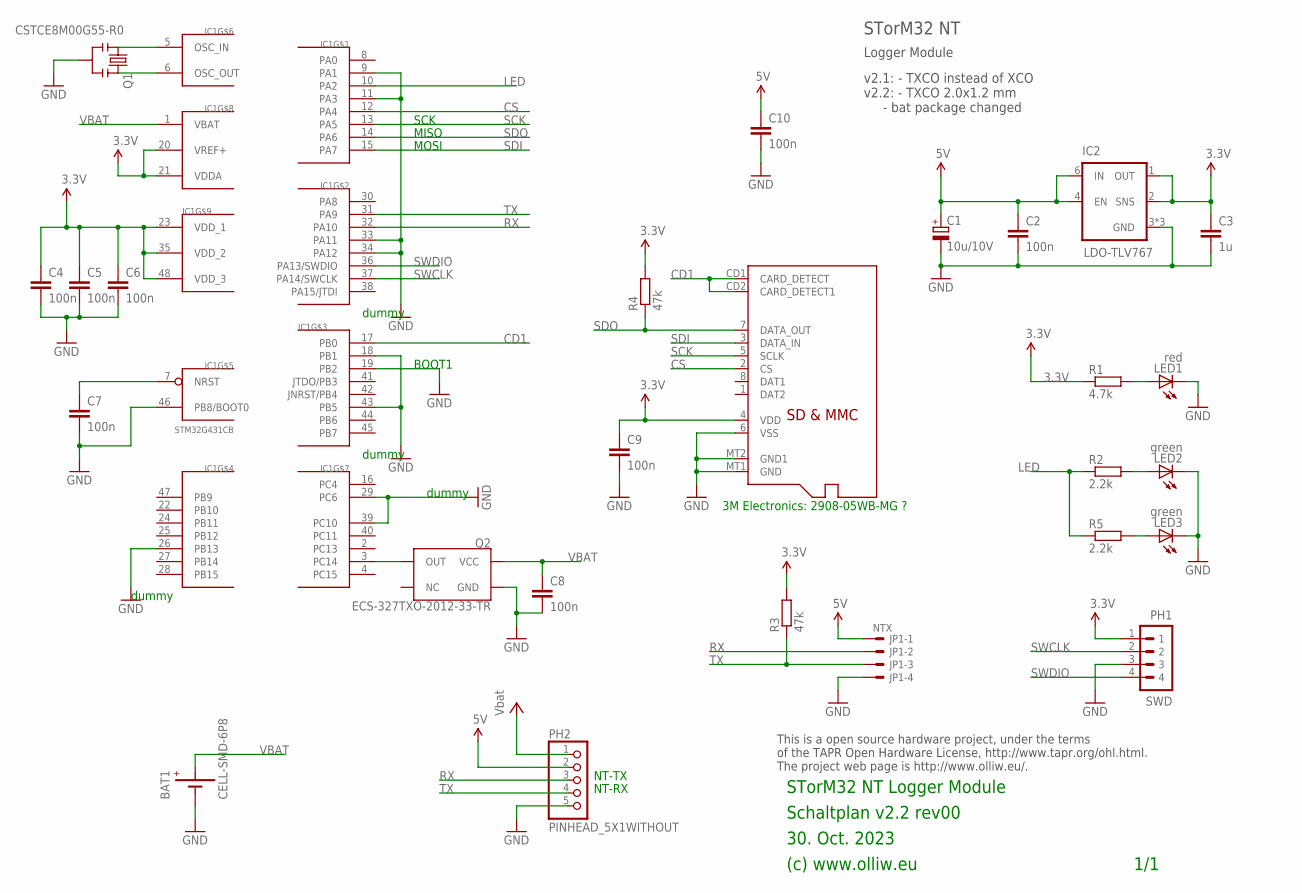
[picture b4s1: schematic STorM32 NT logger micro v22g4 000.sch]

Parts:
BAT1: CELL-SMD-6P8; CELL-RECHARGABLE-6P8
C1: 10u/10V; SMC_B
C2, C10: 100n; C0603
C3: 1u; C0603
C4, C5, C6, C7, C8, C9: 100n; C0402
IC1: STM32G431CB; UFQFPN48
IC2: LDO-TLV767; WSON-6-2X2
JP1: NTX; SM04B-SRSS-TB
LED1: red; CHIPLED_0603
LED2, LED3: green; CHIPLED_0603
PH1: SWD; 4X1_1P27_OCT_BILEX
PH2: PINHEAD_5X1WITHOUT; PINHEAD_5X1_WO
Q1: CSTCE8M00G55-R0; RESONATOR-SMD
Q2: ECS-327TXO-2012-33-TR; TXCO-20X12
R1: 4.7k; R0402
R2, R5: 2.2k; R0402
R3, R4: 47k; R0402
U1: 3M 2908-05WB-MG ??; MICROSD

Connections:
3.3V: C3.1, C4.1, C5.1, C6.1, C9.1, IC1.20 (VREF+), IC1.21 (VDDA), IC1.23 (VDD_1), IC1.35 (VDD_2), IC1.48 (VDD_3), IC2.1 (OUT), IC2.2 (SNS), PH1.1, R1.1, R3.2, R4.2, U1.4 (VDD)
5V: C1.+, C2.1, C10.1, IC2.4 (EN), IC2.6 (IN), JP1.1, PH2.2
CD1: IC1.17 (PB0), U1.CD1 (CARD_DETECT), U1.CD2 (CARD_DETECT1)
CS: IC1.12 (PA4), U1.2 (CS)
GND: BAT1.P- (GND), C1.-, C2.2, C3.2, C4.2, C5.2, C6.2, C7.2, C8.2, C9.2, C10.2, IC1.9 (PA1), IC1.11 (PA3), IC1.18 (PB1), IC1.19 (PB2), IC1.26 (PB13), IC1.29 (PC6), IC1.33 (PA11), IC1.34 (PA12), IC1.39 (PC10), IC1.43 (PB5), IC1.46 (PB8/BOOT0), IC2.3 (GND), IC2.5 (GND), IC2.7 (GND), JP1.4, LED1.C, LED2.C, LED3.C, PH1.3, PH2.5, Q1.2, Q2.2 (GND), U1.6 (VSS), U1.MT1 (GND), U1.MT2 (GND1)
LED: IC1.10 (PA2), R2.1, R5.1
unnamed: C7.1, IC1.7 (NRST)
unnamed: LED2.A, R2.2
unnamed: IC1.5 (OSC_IN), Q1.1
unnamed: IC1.6 (OSC_OUT), Q1.3
unnamed: IC1.3 (PC14), Q2.3 (OUT)
unnamed: LED1.A, R1.2
unnamed: LED3.A, R5.2
RX: IC1.32 (PA10), JP1.2, PH2.3
SCK: IC1.13 (PA5), U1.5 (SCLK)
SDI: IC1.15 (PA7), U1.3 (DATA_IN)
SDO: IC1.14 (PA6), R4.1, U1.7 (DATA_OUT)
SWCLK: IC1.37 (PA14/SWCLK), PH1.2
SWDIO: IC1.36 (PA13/SWDIO), PH1.4
TX: IC1.31 (PA9), JP1.3, PH2.4, R3.1
VBAT: BAT1.P+ (BAT+), C8.1, IC1.1 (VBAT), Q2.4 (VCC)
VCC: PH2.1

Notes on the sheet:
30. Oct. 2023
(c) www.olliw.eu
STorM32 NT Logger Module
Schaltplan v2.2 rev00
This is a open source hardware project, under the terms of the TAPR Open Hardware License, http://www.tapr.org/ohl.html. The project web page is http://www.olliw.eu/.
1/1
Logger Module
STorM32 NT
SCK
MISO
MOSI
BOOT1
dummy
3M Electronics: 2908-05WB-MG ?
NT-RX
NT-TX
v2.1: - TXCO instead of XCO v2.2: - TXCO 2.0x1.2 mm - bat package changed

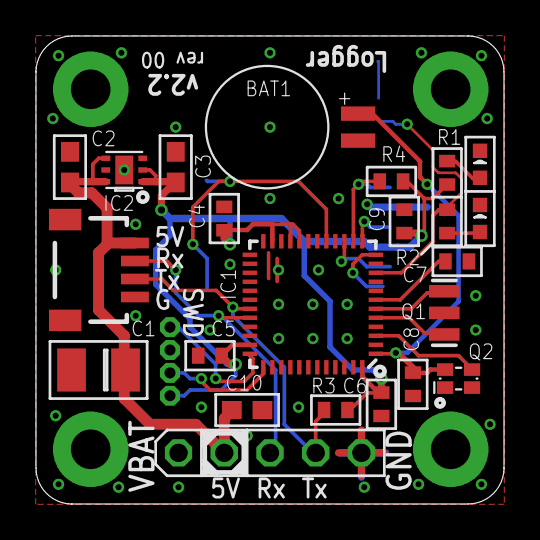
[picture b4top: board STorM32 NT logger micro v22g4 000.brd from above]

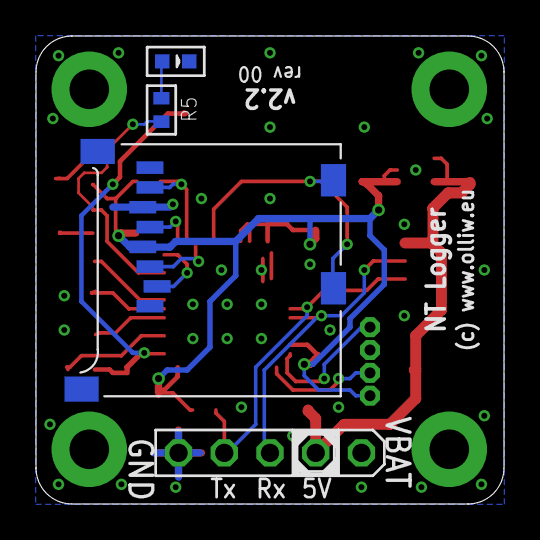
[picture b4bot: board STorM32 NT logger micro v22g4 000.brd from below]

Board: 2 copper layers, 26.0 x 26.0 mm, 27 parts (3 on the bottom side), 21 nets.

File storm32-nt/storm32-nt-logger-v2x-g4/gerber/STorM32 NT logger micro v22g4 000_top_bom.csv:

Comment,Designator,Footprint,LCSC Part #
1u,C3,C0603,
2.2k,R2,R0402,
4.7k,R1,R0402,
10u/10V,C1,SMC_B,
47k,R3 R4,R0402,
100n,C2,C0603,
100n,C4 C5 C6 C7 C8 C9,C0402,
100n,C10,C0603,
CELL-SMD-6P8,BAT1,CELL-RECHARGABLE-6P8,
CSTCE8M00G55-R0,Q1,RESONATOR-SMD,
ECS-327TXO-2012-33-TR,Q2,TXCO-20X12,
LDO-TLV767,IC2,WSON-6-2X2,
NTX,JP1,SM04B-SRSS-TB,
STM32G431CB,IC1,UFQFPN48,
green,LED2,CHIPLED_0603,
red,LED1,CHIPLED_0603,

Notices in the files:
parts and their libraries:
Licensing: CC v3.0 Share-Alike You are welcome to use this library for commercial purposes.
